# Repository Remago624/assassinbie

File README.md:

# Starbie

### front 3D view

### back 3D view

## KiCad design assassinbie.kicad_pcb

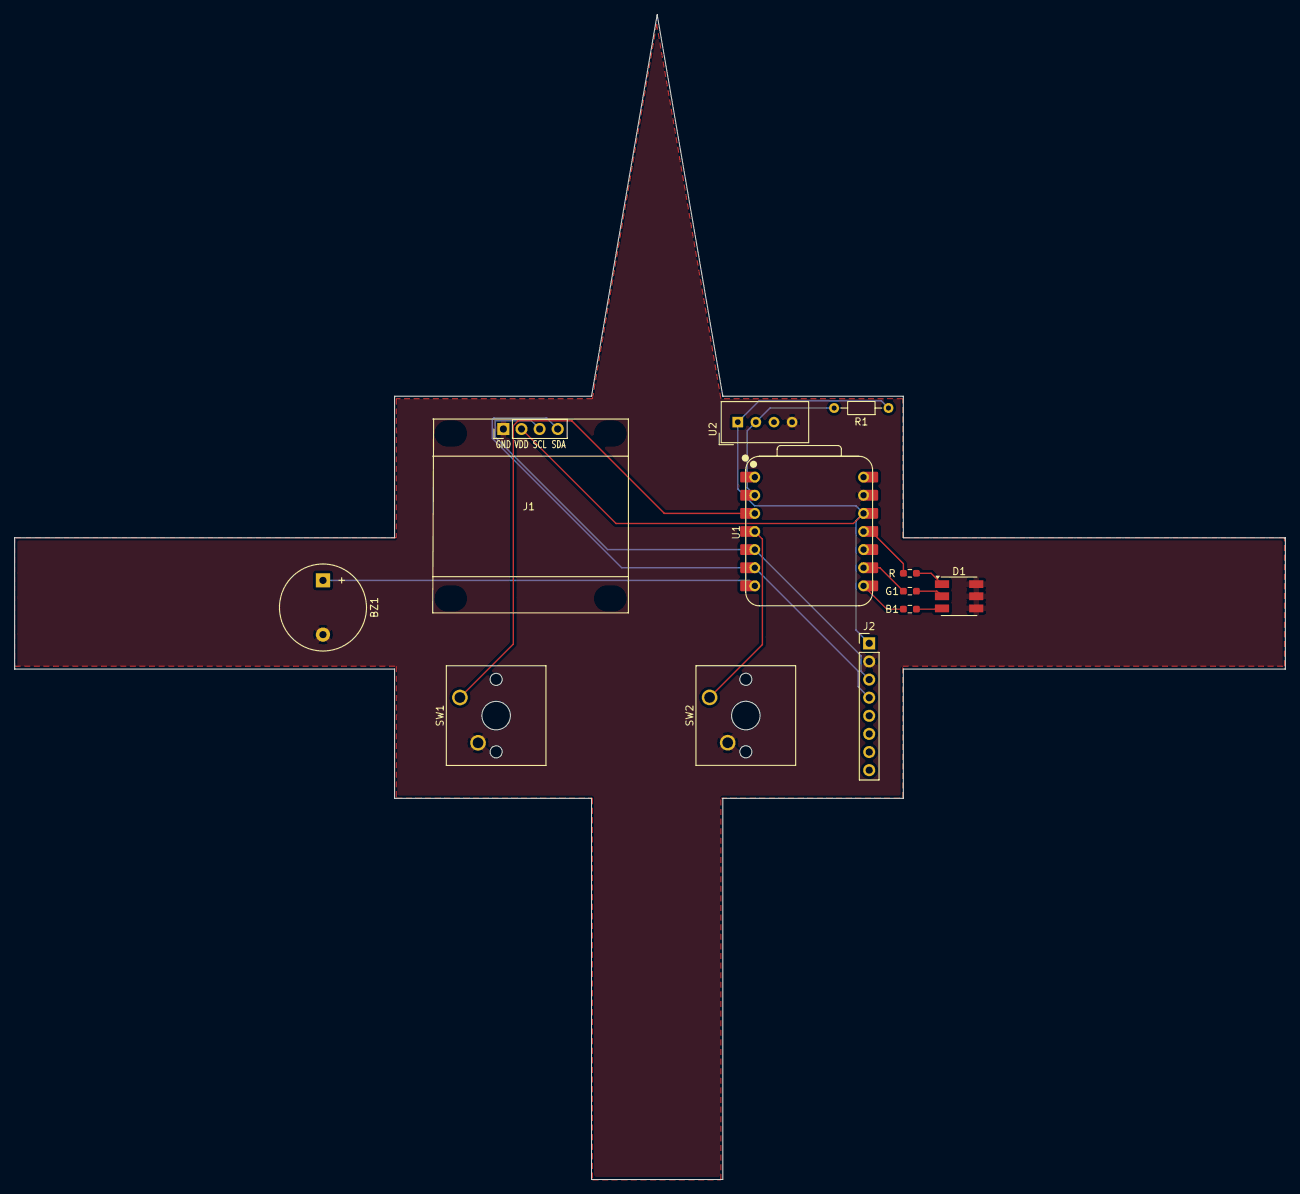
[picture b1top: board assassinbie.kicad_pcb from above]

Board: 2 copper layers, 178.1 x 163.3 mm, 12 parts (0 on the bottom side), 14 nets.

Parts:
B1: 220; R_0603_1608Metric_Pad0.98x0.95mm_HandSolder
BZ1: Buzzer; Buzzer_12x9.5RM7.6
D1: LED_RGB; LED_RGB_5050-6
G1: 220; R_0603_1608Metric_Pad0.98x0.95mm_HandSolder
J1: Conn_01x04_Pin; Display_128x64_096_I2C
J2: Conn_01x08_Pin; PinHeader_1x08_P2.54mm_Vertical
R1: 10k; R_Axial_DIN0204_L3.6mm_D1.6mm_P7.62mm_Horizontal
R2: 220; R_0603_1608Metric_Pad0.98x0.95mm_HandSolder
SW1, SW2: SW_Push; SW_Cherry_MX_1.00u_PCB
U1: XIAO-ESP32-C3-SMD; XIAO-ESP32-C6-DIP
U2: DHT11; Aosong_DHT11_5.5x12.0_P2.54mm

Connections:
+3.3V: J1.2, J2.1, R1.1, U1.12 (3V3_OUT), U2.1 (VDD)
/Blue: B1.2, U1.8 (D7)
/Buzzer: BZ1.1 (+), U1.7 (D6)
/DHT11 DATA: R1.2, U1.2 (D1), U2.2 (DATA)
/GPIO4: SW1.1, U1.3 (D2)
/GPIO5: SW2.1, U1.4 (D3)
/Green: G1.2, U1.9 (D8)
/Red: R2.2, U1.11 (D10)
/SCL: J1.3, J2.3, U1.5 (D4)
/SDA: J1.4, J2.4, U1.6 (D5)
GND: BZ1.2 (-), D1.4 (BA), D1.5 (GA), D1.6 (RA), J1.1, J2.2, SW1.2, SW2.2, U1.13 (GND), U2.4 (GND)
unnamed: B1.1, D1.3 (BK)
unnamed: D1.2 (GK), G1.1
unnamed: D1.1 (RK), R2.1
